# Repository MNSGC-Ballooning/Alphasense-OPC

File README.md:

# Alphasense-OPC
Code to run the ALphasense OPC-N2 optical particle counter using an Arduino. Versions 1 and 2 take advantage of the sensor's STANDALONE mode, and uses active heating (heating pads that turn on/off based on temperature inputs).

OPC_v2: builds off Heater_V2.ino; now uses TWO active heaters. Assumes there is one temperature sensor per heater unit (the first monitors battery temp., the second monitors OPC temp.), and a third temperature sensor measures the atmospheric temperature outside the payload. BE SURE TO NOTE which temperature sensor is which and corresponds to which header in the SD card log!!!!

Email habec021@umn.edu for any questions.

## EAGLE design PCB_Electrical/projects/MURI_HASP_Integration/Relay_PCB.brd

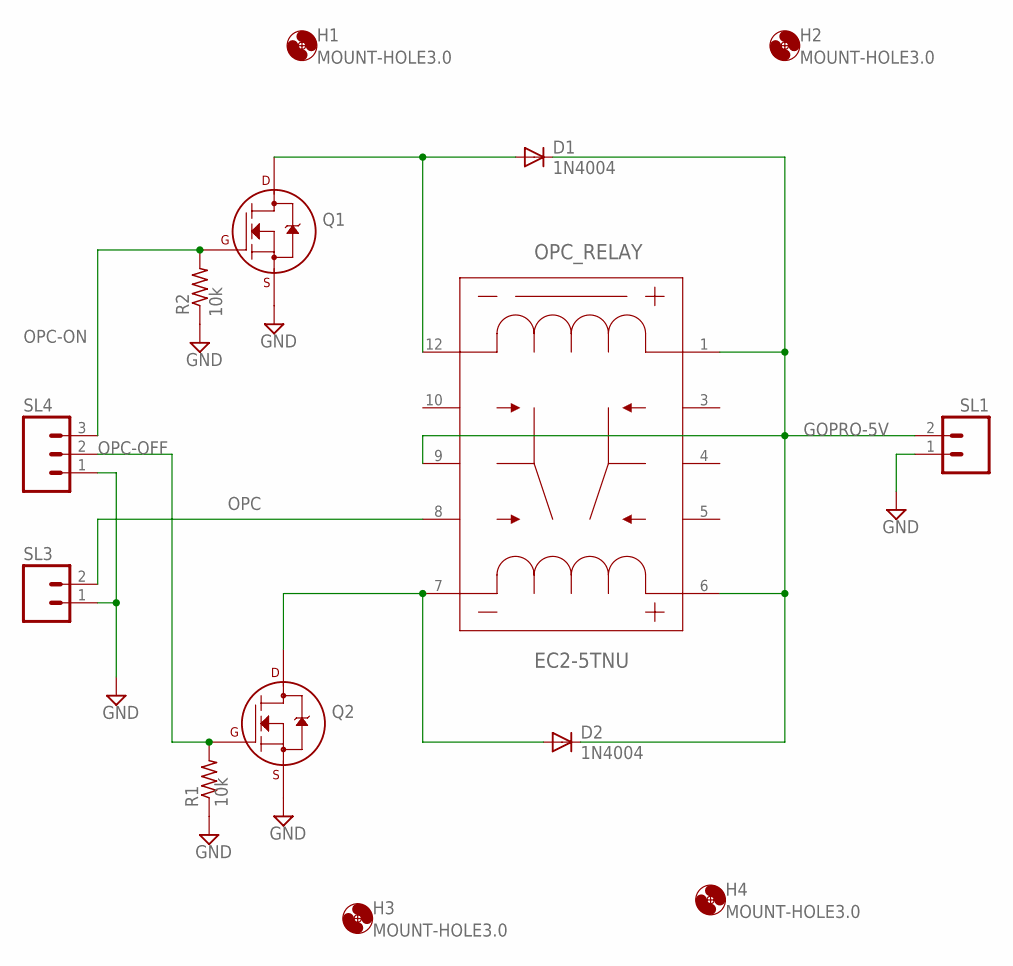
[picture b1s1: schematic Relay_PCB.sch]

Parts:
D1, D2: 1N4004; DO41-10
H1, H2, H3, H4: MOUNT-HOLE3.0; 3,0
OPC_RELAY: EC2-5TNU; EC2TNU
Q1, Q2: 2N7000_TO92; TO-92
R1, R2: R-US_0207/7; 0207/7
SL1, SL3: M02; 02P
SL4: M03; 03P

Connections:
GND: Q1.1 (S), Q2.1 (S), R1.1, R2.1, SL1.1, SL3.1, SL4.1
GOPRO-5V: D1.C, D2.C, OPC_RELAY.1, OPC_RELAY.6 (5), OPC_RELAY.9 (8), SL1.2
unnamed: D1.A, OPC_RELAY.12 (10), Q1.3 (D)
unnamed: D2.A, OPC_RELAY.7 (6), Q2.3 (D)
OPC: OPC_RELAY.8 (7), SL3.2
OPC-OFF: Q2.2 (G), R1.2, SL4.2
OPC-ON: Q1.2 (G), R2.2, SL4.3

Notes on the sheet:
10k

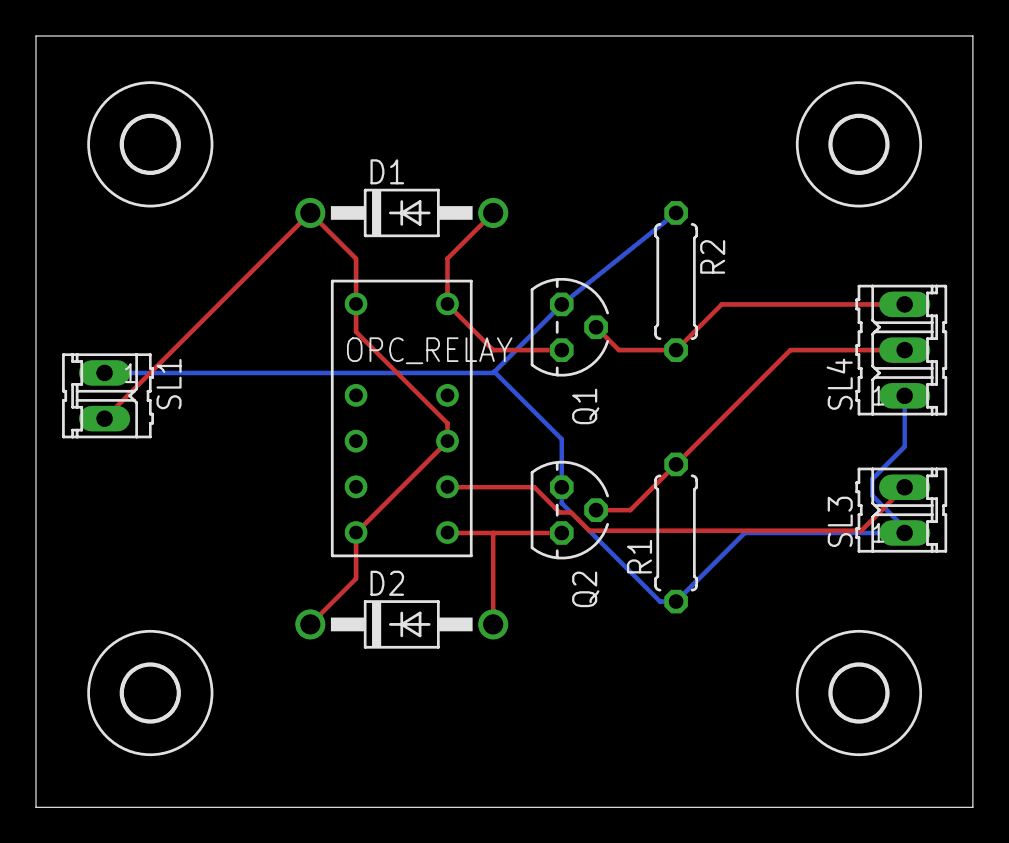
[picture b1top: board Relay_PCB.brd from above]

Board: 2 copper layers, 52.0 x 42.9 mm, 14 parts (0 on the bottom side), 7 nets.

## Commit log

2018-06-11 Added eagle files of HASP PCB and solidworks files of components
2018-06-12 Finalized PCB v1 and generated gerber files
2018-06-13 Implmented sensor suite into OPC payload
2018-09-19 Added files for project schematics and boards that were developed this past summer
2018-11-14 Added changes, don't know what they were lol
